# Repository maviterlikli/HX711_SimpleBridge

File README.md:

<div id="top"></div>

<!-- PROJECT SHIELDS -->
<!--
*** I'm using markdown "reference style" links for readability.
*** Reference links are enclosed in brackets [ ] instead of parentheses ( ).
*** See the bottom of this document for the declaration of the reference variables
*** for contributors-url, forks-url, etc. This is an optional, concise syntax you may use.
*** https://www.markdownguide.org/basic-syntax/#reference-style-links
-->
<!-- 
[![Contributors][contributors-shield]][contributors-url]
[![Forks][forks-shield]][forks-url]
[![Stargazers][stars-shield]][stars-url]
[![Issues][issues-shield]][issues-url]
[![MIT License][license-shield]][license-url]
[![LinkedIn][linkedin-shield]][linkedin-url]
-->

<!-- PROJECT LOGO 
<br />
<div align="center">

  <h3 align="center">Best-README-Template</h3>

  <p align="center">
    An awesome README template to jumpstart your projects!
    <br />
    <a href="https://github.com/othneildrew/Best-README-Template"><strong>Explore the docs »</strong></a>
    <br />
    <br />
    <a href="https://github.com/othneildrew/Best-README-Template">View Demo</a>
    ·
    <a href="https://github.com/othneildrew/Best-README-Template/issues">Report Bug</a>
    ·
    <a href="https://github.com/othneildrew/Best-README-Template/issues">Request Feature</a>
  </p>
</div>
-->

<!-- TABLE OF CONTENTS 
<details>
  <summary>Table of Contents</summary>
  <ol>
    <li>
      <a href="#about-the-project">About The Project</a>
      <ul>
        <li><a href="#built-with">Built With</a></li>
      </ul>
    </li>
    <li>
      <a href="#getting-started">Getting Started</a>
      <ul>
        <li><a href="#prerequisites">Prerequisites</a></li>
        <li><a href="#installation">Installation</a></li>
      </ul>
    </li>
    <li><a href="#usage">Usage</a></li>
    <li><a href="#roadmap">Roadmap</a></li>
    <li><a href="#contributing">Contributing</a></li>
    <li><a href="#license">License</a></li>
    <li><a href="#contact">Contact</a></li>
    <li><a href="#acknowledgments">Acknowledgments</a></li>
  </ol>
</details>
-->

<!-- ABOUT THE PROJECT -->
## About The Project

<!-- [![Product Name Screen Shot][product-screenshot]](https://example.com) -->

This is a simple PCB that is designed to work with commonly found HX711 Arduino module. So, this is an extension to the original HX711 module shown below.

This is still under work. Design is finished. However, I am still writing the manual. As you can see, even for first grade electronical engineering students, there is nothing hard or important about this repo, since this is a simple Wheatstone bridge for HX711 module. However, while I work in my university, several students from computer sciences and engineering departments required a simple Wheatstone bridge for strain gauge applications. This was a design for a really primitive strain reader. It will not be useful in data acquisition applications, but it will help you learn if you are a new starter to strain gauge applications. It will, also, give you a great trick to easily calibrate your system or readings. A calibration that does not only calibrates the IC, but calibrates the whole system.

<b>Why do you need a PCB when you can do new-starter-things on breadboard?</b>

Since Wheatstone bridges are highly sensitive, it is impossible to acquire data on breadboards. If you like to see why, build a Wheatstone bridge on breadboard with any 24bit ADC and softly blow on the breadboard. The readings will go crazy. Also, any use of standard breadboard jumpers will have the same effect. This SIMPLE one sided PCB is to minimize such environmental effect. 

<b>BE CAREFUL!</b>
<br>
This PCB is designed to work with HW-27 Arduino module. However, it will work for the modules that has the same "J1" (see picture below) pin configuration.

<p align="right">(<a href="#top">back to top</a>)</p>

### Built With

The design and schematics are made in Eagle. I aim to add universal data packages as well. However, if you would like to change the dimensions, packages, or anything else, Eagle is a free software right now.

* [Eagle](https://www.autodesk.com/products/eagle/free-download)

<p align="right">(<a href="#top">back to top</a>)</p>

<!-- GETTING STARTED -->
## Getting Started

There are several ways to use the PCB. It mainly depends on your budget and required output quality. NO DOT FORGET that HX711 is not an IC that a medium or advanced strain reader can be designed from. With that in mind, if you want to use the bridge, you can simply produce it however you want, but do not spend too much money on this. 

If you are going to use HX711 with load cells, this is not for you. This repo is basically for an adapter to use strain gauges with HX711. A simple extension.

If you are going to use strain gauges and would like to read the ADC data with HX711, please do continue.

After this point, every value, name or component will be refered to the following image, if otherwise not stated. Take the image as reference. 

### Prerequisites

First of all, you need to know basics of Wheatstone bridge, and calculations. If you do not know where to start, HBM provides a good start-up knowledge [here](https://www.hbm.com/en/7163/wheatstone-bridge-circuit/). If you already have another source, you can use that as well, but be careful of resistor names, excitation points and reading points. They will vary.

You are required to know how ADC output works. It is simply a bit value converted to decimal, which has the maximum decimal value as maximum voltage and minimum decimal value as your minimum voltage. Maximum and minimum decimal values are dependent on your ADC bit resolution. For HX711, in data sheet it is given as "The output 24 bits of data is in 2’s complement format. When input differential signal goes out of the 24 bit range, the output data will be saturated at 800000h (MIN) or 7FFFFFh (MAX), until the input signal comes back to the input range"
So;

800000h will be equal to -8388608

7FFFFFh will be equal to +8388607 in decimal.
### Choosing the Strain Gauge

In here, if you already have a strain gauge, use that. However, if you do not have any strain gauges, there are 3 ohm values: 120, 350, 1000 ohms. Choose as you like, but remember you will need to buy resistors according to those values. So be careful if you will be able to supply resistors.

Quality of the strain gauges is totally up to your budget. If this is your first time, buy the cheap ones. However, be careful to get EXACT gauge factor. Without exact factor, you can not convert ADC readings to meaningful strain values. This value is not SAME all over a single product from a single factory. High end suppliers measure and give exact strain gauge factor for every batch of gauges.

You will require following resistors for following strain gauge resistance values. 

Assuming quarter-bridge configuration with trimpot as zero-balancer;

| Strain Gauge  | Required Resistors | Required TrimPots|
| ------------- | ------------- | ------------- |
| Ohm  | NumberofResistorsxOhm | NumberofTrimpotsxOhm |
| 350 Ω  | 3x330   | 1x50 |

Secondly, how we calculate the resistor values is this. Assume R2 to be your strain gauge, so 120 Ω, 350 Ω or 1000 Ω. For the PCB above, <b>(R4+RT/2)/(R1+RT/2)</b> should be equal or really close to <b>R2/R3</b>. In here, if you have a really minor imbalance, it can be corrected by trimpot. You can decide your resistor values like this, or you can use my implementation, which will be based on 350 Ω stain gauges and most common resistor values. BE CAREFUL your choose of resistors will effect the output. So you may need to do more calculations.

So, if we chose 350 Ω strain gauge, and 330 Ω commonly found resistors for R1, R3 and R4, as a trimpot 50 Ω for RT, and set the trimpot to divide resistance 36 Ω to 14 Ω (which 36 Ω should be added serially to R1) system ALMOST balances. So balance equation becomes;
| Left Side  | Right Side |
| ------------- | ------------- |
| 1.063953488  | 1.060606061  |

Remaining unbalance can be corrected with trimpot easily.

<b> As a final important note, DO NOT USE</b> your strain gauges without properly gluing it to a proper reading surface. Strain gauges consists of a thin backing layer, which will not stand usage on their on. Find a piece of metal, plastic or anything, apply the strain gauge with a proper and strong adhesive, use strain gauge terminal to increase the cable dimension, and make sure your cables are not going to rip off. It is really easy to damage the cables of strain gauge.

### Choosing Bridge Structure
In here, the first thing you need to know is if you are going to need a manual way to zero balance the bridge. This depends on several things like resistor tolerances, ADC gain (PGA) and required reading range. Simply, if you are using high gain with high tolerances, your zero reading may be off scale already. In that case, your system will not work at all.

So, if you are using %5 tolerance resistors with the implementation given in the <b>Choosing the Strain Gauge</b> topic, due to resistor tolerances, there can be up to 0.25 V initial imbalance. However, at the largest reading range, (5 V excitation, 32 gain) HX711 will read voltages between +0.078125 V and -0.078125 V. As you can see, the resistor tolerances will shift your output to out of range. This is why a trimpot is used in the system to zero-balance the bridge.

The only case you can implement the given bridge without trimpot is if you have 0.1% tolerance resistors which are quite expensive. It would not be logical to dump so much money into a system of this quality. So, if you do not know better, use trimpot to zero balance the system, so you can use cheap solutions. Also, in this tolerance calculation, resistance of PCB pathways are neglected. If you include pathway resistances, tolerances, and PCB quality becomes much tighter, meaning even more expensive.

So, if you use 

330 Ω resistors for R1, R3 and R4,

350 Ω strain gauge for R2,

and 50 Ω trimpot for RT

you will make the bridge work. However, this implementation will make things a bit harder later on, in calibration, but it will be nothing that a little math cannot solve.

### Choosing Shunt Calibration Resistors
Shunt calibration resistors are used to apply a virtual strain to the system. Since the applied values of resistors are known and output can be obtained, system can be calibrated. [There](http://www.vishaypg.com/docs/11064/tn514.pdf) is an excellent guide on how to use and calculate shunt calibration. In this implementation, I am going to use 2 resistors, since we have much higher tolerances and not so sensitive bridge. Choosing the resistor values depends on your reading range. It is better to apply higher strains, which means lower resistor values on shunt calibration. However, it cannot exceed the reading range of the ADC. So ideally, if you apply 10 kΩ parallel resistor to system (as RS1 or RS2) you will cause 0.043005 V shift in ADC reading. Since 32 gain measures voltages between +0.078125 V and -0.078125 V, this will work. However, 128 gain and 64 gain will have a reading range of ±0.01953125 V and ±0.0390625 V, respectively. 10 kΩ shunt calibration resistors will not work for 128 and 64 gain, since it will shift the value out of range. 

<b> If you do not know which gain you are going to use, 50 kΩ and 100 kΩ shunt calibration resistors will work fine.</b>

<p align="right">(<a href="#top">back to top</a>)</p>

### List of Components
To use my implementation with 350 Ω strain gauges, you will need;

- 3 x 330 Ω resistor (prefer metal film, or as low tolerance as can be)
- 1 x 50 Ω trimpot (prefer as much turn as possible. Usually I use 20 turn)
- 1 x 2 pin connector (to your preference)
- 3 x DIP Switch
- 1 x 50 kΩ resistor for RS1
- 1 x 100 kΩ resistor for RS2

<p align="right">(<a href="#top">back to top</a>)</p>

### Preliminary Measurements
This step is the most important step. To have a proper measurement, you have to know your resistor values. You can use a simple multimeter, or anything more advanced. My procedure is as follows;
1. Measure R1, R3, R4 and RT, and SAVE them somewhere you will not misplace.
2. (optional) If you want more precision, you can measure the PCB pathway resistances and add them to proper resistor values. 
3. ONLY solder the RS1, RS2 and DIP switch that connects shunt calibration resistors to the main bridge. 
4. Measure the resistor values at the ends of RS2 (be careful R2 should not be soldered yet, or any other components.) in 3 possible states and SAVE them somewhere you will not misplace. 3 possible states are;
    - switch1 (RS1) on, switch2 (RS2) off
    - switch1 (RS1) off, switch2 (RS2) on
    - switch1 (RS1) on, switch2 (RS2) on
5. You can now solder the remaining parts.

<p align="right">(<a href="#top">back to top</a>)</p>

### Soldering

It is assumed that the PCB is one sided and components are on the other face of the copper layer. However, since all the components are passive, you can switch sides, except HX711 pins.

BE CAREFUL to follow soldering order given in <b>Preliminary Measurements</b> to obtain best results.

There are 2 elements to every component at a Wheatstone bridge, a resistor and a connector. Connector is to add strain gauge to system, and resistors are static components. So, if you are going to use quarter-bridge, DO NOT solder X1, X3 and X4 connectors, but solder R1, R3 and R4 resistors. To add the strain gauge, DO NOT solder R2 resistor, but solder X2 connector. For other bridge implementations, logic is same. So, you eighter use a connector or a resistor.

## Calibration

If you are going to calibrate the system with any other method, or if you do not require a calibration, you may skip this step. But if you need calibration, we will conduct a Ax+B calibration.

To do so, it is required to know shunt calibration resistor values, bridge resistor values and virtual strain that is applied by shunt calibration resistors. Assuming R1, R3 and R4 to be static, 

Epsilon_s = -R_G/(F_G*(R_G+R_S))

where;

Epsilon_s   : Strain on the strain gauge (m/m)
R_G         : Strain gauge resistance value (Ω)
R_C         : Shunt calibration resistor value (Ω)
F_G         : Strain gauge factor (must be given by supplier)

By conducting the calculation for every state of RS1 and RS2 switch, you will have 3 strain values and 3 outputs from the ADC. You do not have to but you can also add your zero reading (not perfectly zero) to this data set, which makes 4 strain values and 4 ADC outputs (given as Parameters in <b>Usage</b>). Only remaining thing is to linearly convert ADC values to match strain values. 
1. First thing I suggest you to do is a check of system. To do that, take your readings (4 state of switch (R_G), 4 ADC output) and calculate linear regression error. As an alternative, you can use Microsoft Excel (or any other related software) draw the diagram of data as scatter graph, then make Excel to calculate equation and R^2 value. If your R^2 value is really close to 1, you have a good working system.
2. By applying the calculations above, you should have 4 strain values (Epsilon_s).
3. Take the values from ADC output that are designated as <b>Parameter: ADCout0, ADCout1, ADCout2, ADCout3 </b>
4. Make a table.

| Strain values | ADC Outputs |
| ------------- | ------------- |
| Epsilon_s=0 | ADCout0 |
| Epsilon_s RS1 | ADCout1 |
| Epsilon_s RS2 | ADCout2 |
| Epsilon_s Rs1 and RS2 | ADCout3 |

5. Calculate the number that you need to multiply and add with ADCout to match with epsilon values.

For example,
| Strain values | ADC Outputs | ADCout x A + B | Calibrated Output |
| ------------- | ------------- | ------------- | ------------- |
| 0 | 1000 |  1000 x -0.00001 + 0.01 | 0 |
| -0.01 | 2000 | 2000 x -0.00001 + 0.01 | -0.01 |
| -0.02 | 3000 | 3000 x -0.00001 + 0.01 | -0.02 |
| -0.03 | 4000 | 4000 x -0.00001 + 0.01 | -0.03 |

<b> Readings in this method are always gives results in compressive strain.</b>

## Usage
First of all, you need to select a channel, POSITIVE_CHANNEL_SELECT and NEGATIVE_CHANNEL_SELECT switches are made for that. I added this switches and I have not tested it. It is simply to direct signal to channels. This may not be necessary. If you are sure you do not need that, you can short the connections. However, if you are going to use;

If you are going to use channel A, 
- set POSITIVE_CHANNEL_SELECT, 1st to off and 2nd to on
- set NEGATIVE_CHANNEL_SELECT, 1st to off and 2nd to on

If you are going to use channel B, 
- set POSITIVE_CHANNEL_SELECT, 1st to on and 2nd to off
- set NEGATIVE_CHANNEL_SELECT, 1st to on and 2nd to off

Make sure switch of RS1 and RS2 are open (is not connected to system) (off).

Then power-up the system and take ADC readings. Turn the trimpot RT until you get a zero or near zero reading. Take a several second stable reading, take the average and save. <b>Parameter: ADCout0</b>

<b>IMPORTANT NOTE:</b> DO NOT use any code that has in-code zero function (tare). Make sure that you are seeing the direct output of the ADC

After you have your zero level; 
- Close switch that is connected to RS1, take a several second stable reading, take the average and save. <b>Parameter: ADCout1</b>
- Close switch that is connected to RS2, take a several second stable reading, take the average and save. <b>Parameter: ADCout2</b>
- Close switches that is connected to RS1 and RS2, take a several second stable reading, take the average and save. <b>Parameter: ADCout3</b>
- 
<b> While calibrating, DO NOT change the strain of the material your strain gauge is placed. Make sure there are no external loads on measured part.</b>
<b> While closing and opening switches, please wait for system to converge.</b>

After this step, open the switches of RS1 and RS2. Now, you are ready to take your strain reading. In this method, you will convert your readings into meaningful strain values after you completed strain readings. However, after calculating necessary calibration values, you can input those values to your code that reads ADC as well. 

<p align="right">(<a href="#top">back to top</a>)</p>

## License

This is not licensed. You can steal it. 
<p align="right">(<a href="#top">back to top</a>)</p>

<!-- CONTACT -->
## Contact

Fahri Emre Özdemir - [@linkedin](https://www.linkedin.com/in/fahriemreozdemir/)

Project Link: [HX711_SimpleBridge](https://github.com/maviterlikli/HX711_SimpleBridge/)

<p align="right">(<a href="#top">back to top</a>)</p>

<!-- MARKDOWN LINKS & IMAGES -->
<!-- https://www.markdownguide.org/basic-syntax/#reference-style-links -->
[contributors-shield]: https://img.shields.io/github/contributors/othneildrew/Best-README-Template.svg?style=for-the-badge
[contributors-url]: https://github.com/maviterlikli/HX711_SimpleBridge/graphs/contributors
[forks-shield]: https://img.shields.io/github/forks/othneildrew/Best-README-Template.svg?style=for-the-badge
[forks-url]: https://github.com/maviterlikli/HX711_SimpleBridge/network/members
[stars-shield]: https://img.shields.io/github/stars/othneildrew/Best-README-Template.svg?style=for-the-badge
[stars-url]: https://github.com/maviterlikli/HX711_SimpleBridge/stargazers
[issues-shield]: https://img.shields.io/github/issues/othneildrew/Best-README-Template.svg?style=for-the-badge
[issues-url]: https://github.com/maviterlikli/HX711_SimpleBridge/issues
[license-shield]: https://img.shields.io/github/license/othneildrew/Best-README-Template.svg?style=for-the-badge
[license-url]: https://github.com/maviterlikli/HX711_SimpleBridge/blob/master/LICENSE.txt
[linkedin-shield]: https://img.shields.io/badge/-LinkedIn-black.svg?style=for-the-badge&logo=linkedin&colorB=555
[linkedin-url]: https://linkedin.com/in/fahriemreozdemir
[product-screenshot]: images/screenshot.png

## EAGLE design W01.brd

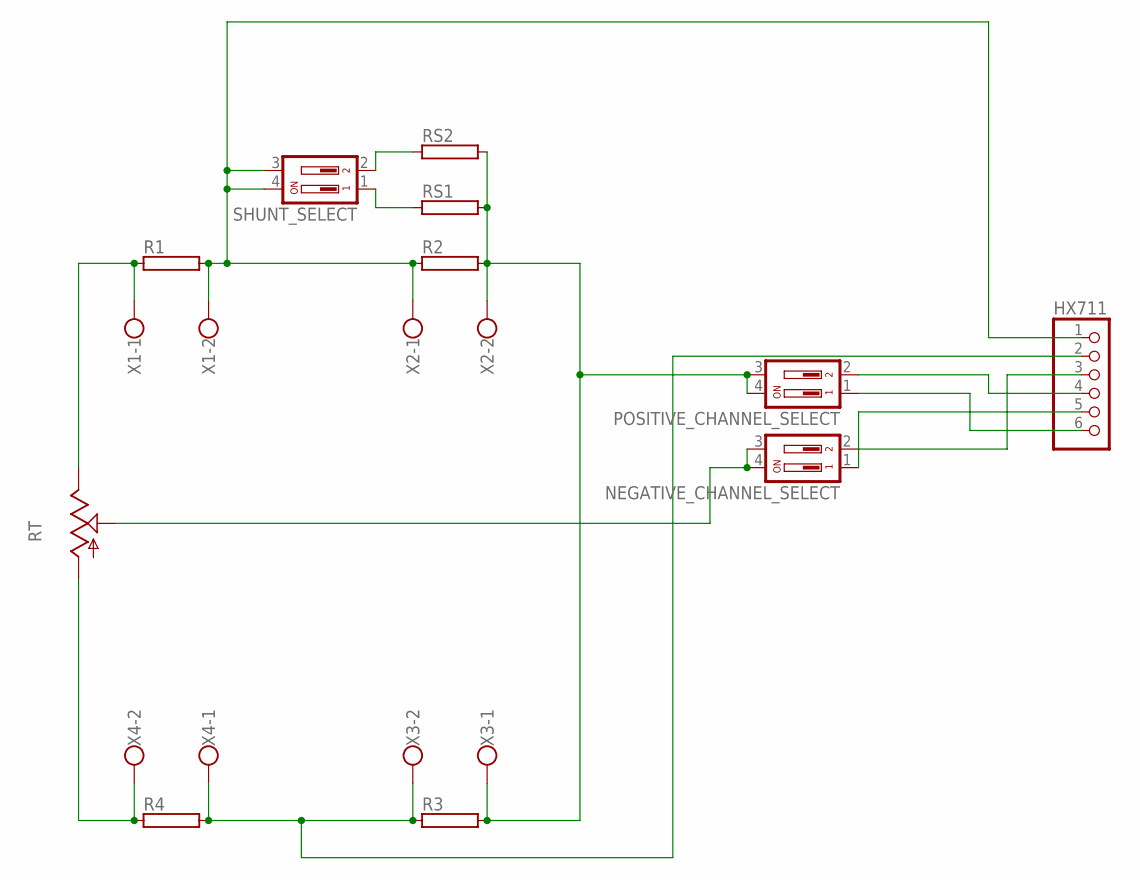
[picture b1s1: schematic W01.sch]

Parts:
HX711: PINHD-1X6; 1X06
NEGATIVE_CHANNEL_SELECT: DIP02YL
POSITIVE_CHANNEL_SELECT: DIP02YL
R1, R2, R3, R4: RAC03; AC03
RS1, RS2: RAC03; AC03
RT: TRIM_US-RJ9W; RJ9W
SHUNT_SELECT: DIP02YL
X1, X2, X3, X4: W237-102

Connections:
unnamed: HX711.1, R1.2, R2.1, SHUNT_SELECT.3, SHUNT_SELECT.4, X1.2, X2.1
unnamed: RS2.1, SHUNT_SELECT.2
unnamed: HX711.2, R3.1, R4.2, X3.2, X4.1
unnamed: R1.1, RT.E, X1.1
unnamed: R4.1, RT.A, X4.2
unnamed: HX711.4, POSITIVE_CHANNEL_SELECT.2
unnamed: HX711.6, POSITIVE_CHANNEL_SELECT.1
unnamed: HX711.5, NEGATIVE_CHANNEL_SELECT.1
unnamed: HX711.3, NEGATIVE_CHANNEL_SELECT.2
unnamed: POSITIVE_CHANNEL_SELECT.3, POSITIVE_CHANNEL_SELECT.4, R2.2, R3.2, RS1.2, RS2.2, X2.2, X3.1
unnamed: NEGATIVE_CHANNEL_SELECT.3, NEGATIVE_CHANNEL_SELECT.4, RT.S
unnamed: RS1.1, SHUNT_SELECT.1

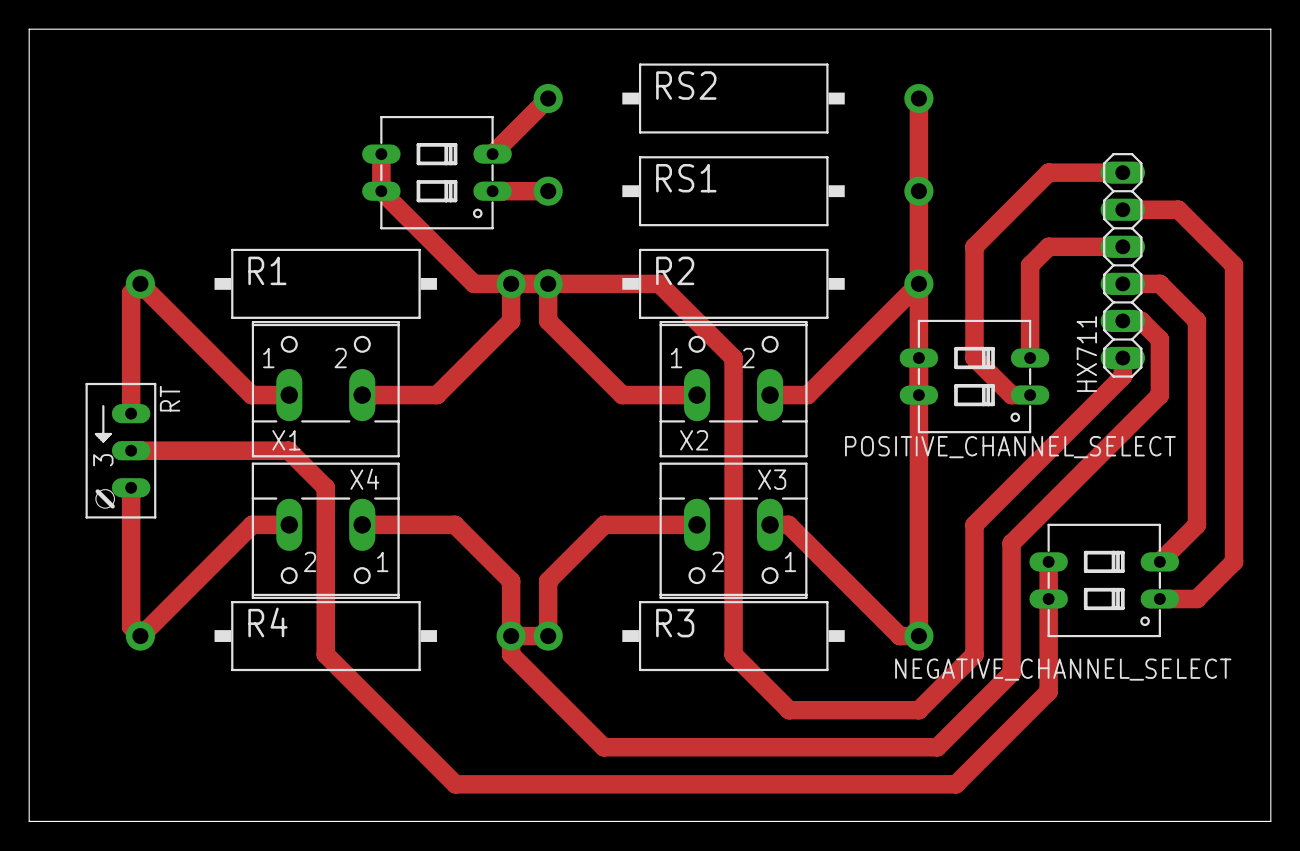
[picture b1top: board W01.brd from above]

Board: 2 copper layers, 85.1 x 54.3 mm, 15 parts (0 on the bottom side), 12 nets.

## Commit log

2022-02-02 Create LICENSE

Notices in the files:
README.md:
This is not licensed. You can steal it.
